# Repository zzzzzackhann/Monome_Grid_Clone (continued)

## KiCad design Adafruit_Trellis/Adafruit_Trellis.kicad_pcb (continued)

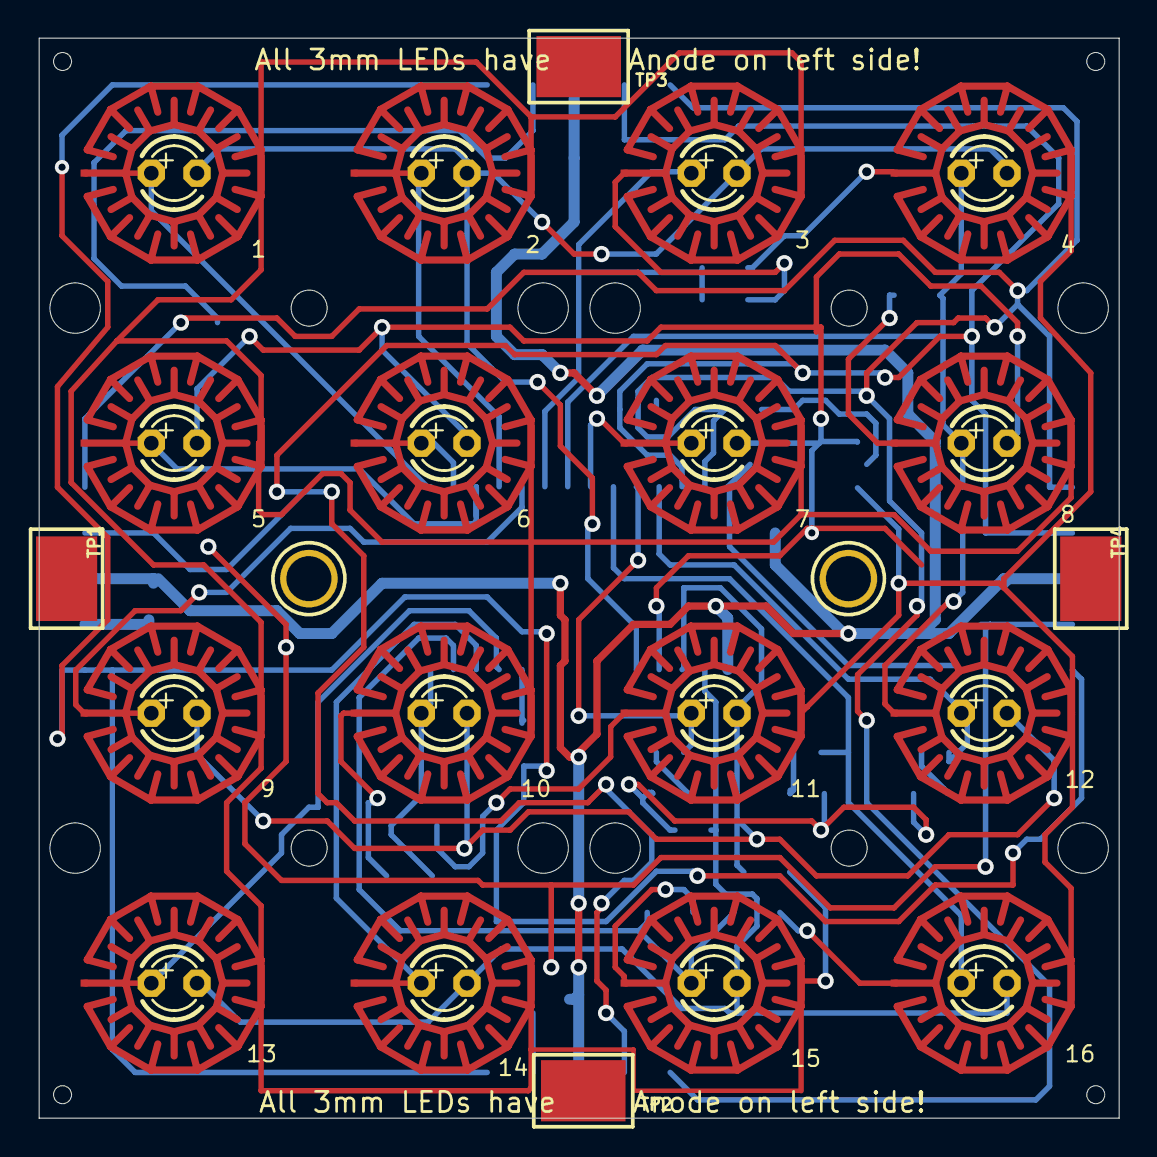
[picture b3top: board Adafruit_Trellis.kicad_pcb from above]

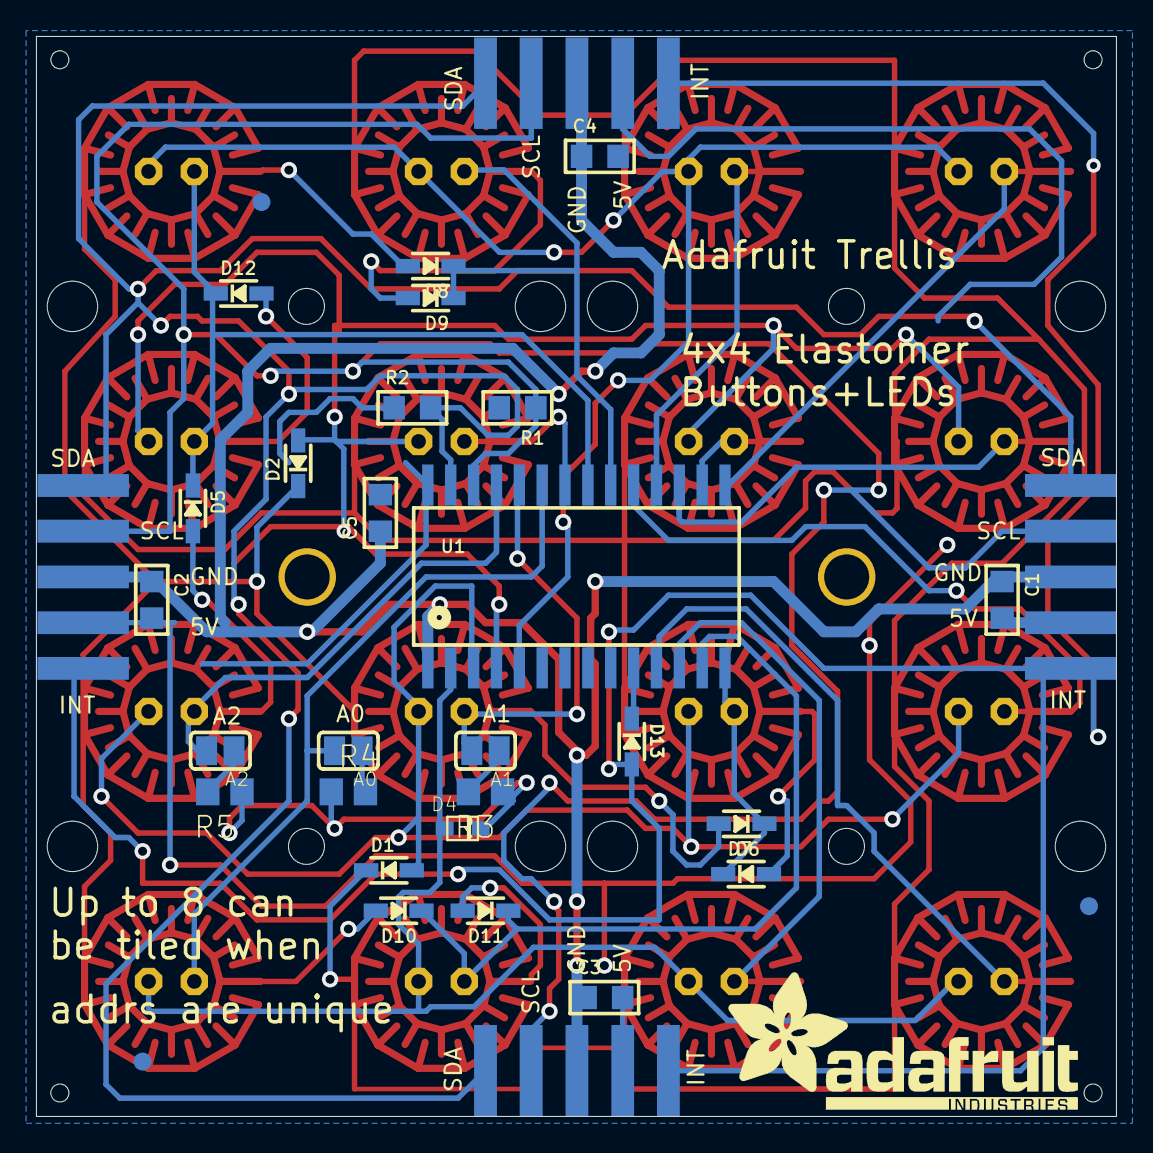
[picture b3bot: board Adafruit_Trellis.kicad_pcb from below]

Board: 2 copper layers, 60.0 x 60.0 mm, 42 parts (34 on the bottom side), 39 nets.

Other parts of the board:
U$3: ADAFRUIT_TEXT_20MM

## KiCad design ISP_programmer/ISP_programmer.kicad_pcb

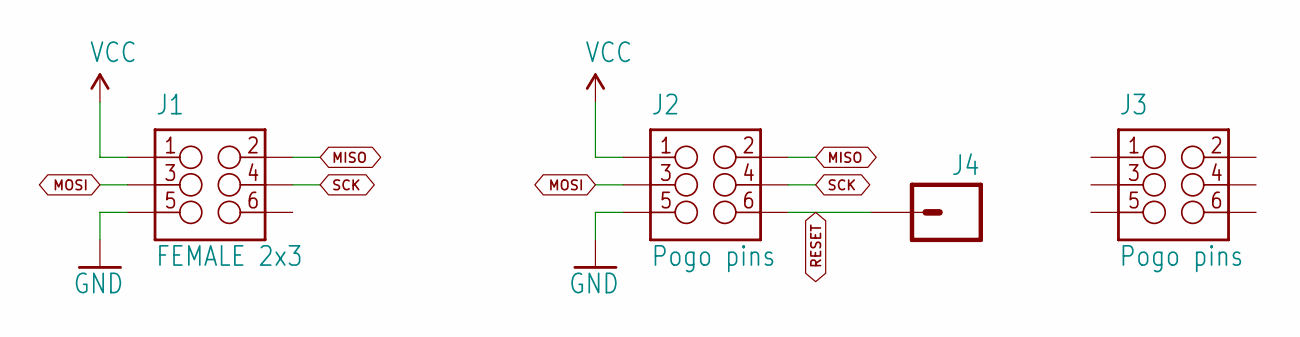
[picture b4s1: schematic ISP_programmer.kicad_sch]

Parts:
J1: FEMALE 2x3; 2X3
J2, J3: Pogo pins; 2X3_POGO
J4: M01PTH; 1X01

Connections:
GND: J1.5, J2.P$5 (5)
MISO: J1.2, J2.P$2 (2)
MOSI: J1.3, J2.P$3 (3)
RESET: J2.P$6 (6), J4.1
SCK: J1.4, J2.P$4 (4)
VCC: J1.1, J2.P$1 (1)

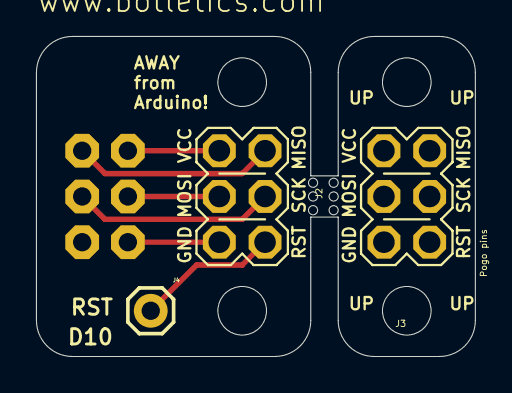
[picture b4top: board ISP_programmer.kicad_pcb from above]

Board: 2 copper layers, 24.4 x 17.8 mm, 14 parts (1 on the bottom side), 6 nets.

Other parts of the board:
UNK_HOLE_0: dummyfp0
UNK_HOLE_1: dummyfp1
UNK_HOLE_2: dummyfp2
UNK_HOLE_3: dummyfp3
UNK_HOLE_4: dummyfp4
UNK_HOLE_5: dummyfp5
UNK_HOLE_6: dummyfp6
UNK_HOLE_7: dummyfp7
UNK_HOLE_8: dummyfp8
UNK_HOLE_9: dummyfp9
